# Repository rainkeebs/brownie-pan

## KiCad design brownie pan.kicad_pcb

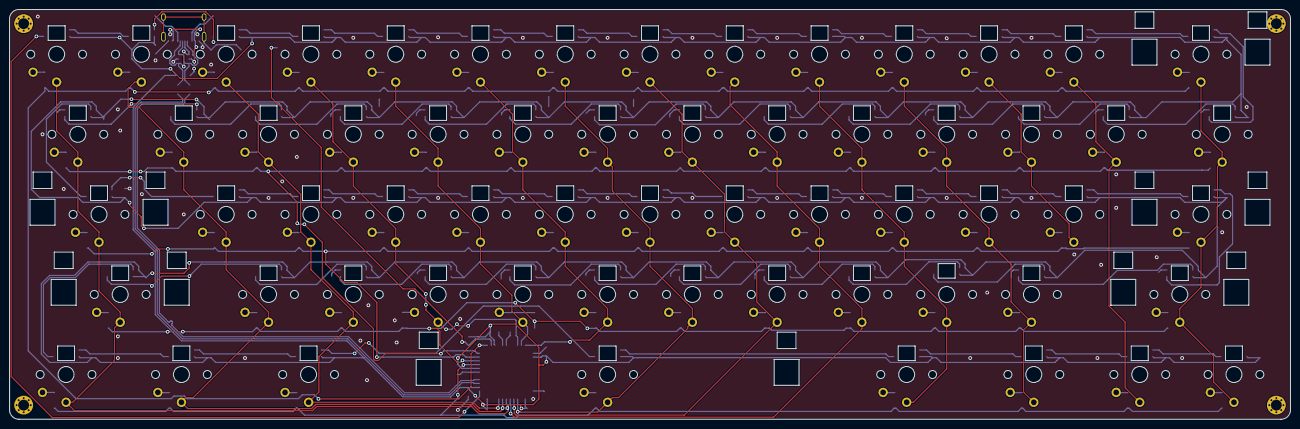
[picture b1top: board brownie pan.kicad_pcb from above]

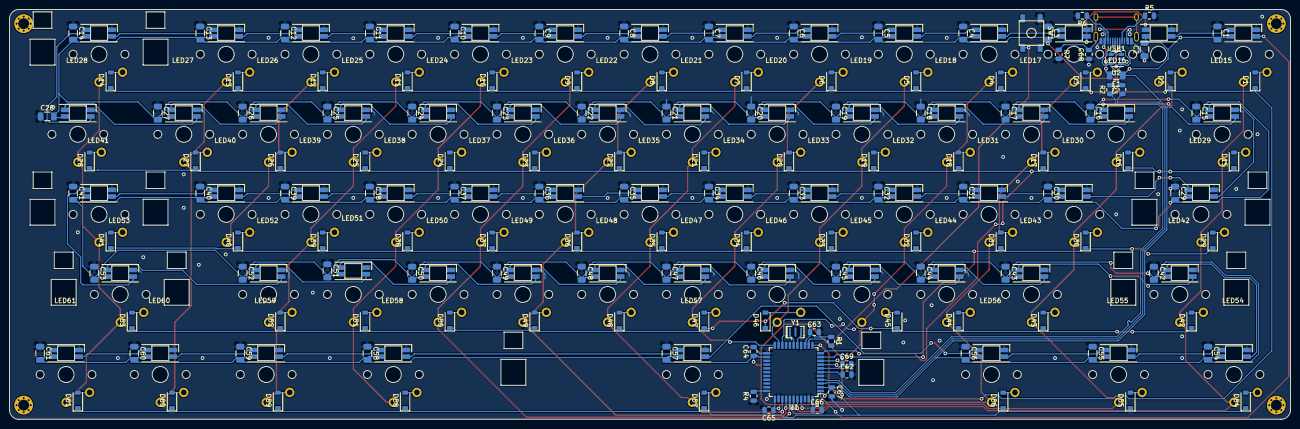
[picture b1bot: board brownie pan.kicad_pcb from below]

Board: 2 copper layers, 272.0 x 87.0 mm, 269 parts (204 on the bottom side), 156 nets.

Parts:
C1, C2, C3, C4, C5, C6, C7, C8, C9, C10, C11, C12, C13, C14, C15, C16, C17, C18, C19, C20, C21, C22, C23, C24, C25, C26, C27, C28, C29, C30, C31, C32, C33, C34, C35, C36, C37, C38, C39, C40, C41, C42, C43, C44, C45, C46, C47, C48, C49, C50, C51, C52, C53, C54, C55, C56, C57, C58, C59, C60, C61: 100uF; C_1206_3216Metric
C62: 1uF; C_0805_2012Metric
C63, C64, C65, C66, C69: 0.1uF; C_0805_2012Metric
C67: 10uF; C_0805_2012Metric
C68: 4.7n; C_0805_2012Metric
D1, D2, D3, D4, D5, D6, D7, D8, D9, D10, D11, D12, D13, D14, D15, D16, D17, D18, D19, D20, D21, D22, D23, D24, D25, D26, D27, D28, D29, D30, D31, D32, D33, D34, D35, D36, D37, D38, D39, D40, D41, D42, D43, D44, D45, D46, D47, D48, D49, D50, D51, D52, D53, D54, D55, D56, D57, D58, D59, D60, D61: D_Small; D_SOD-123
F1: 500mA; Fuse_1206_3216Metric
LED1, LED2, LED3, LED4, LED5, LED6, LED7, LED8, LED9, LED10, LED11, LED12, LED13, LED14, LED15, LED16, LED17, LED18, LED19, LED20, LED21, LED22, LED23, LED24, LED25, LED26, LED27, LED28, LED29, LED30, LED31, LED32, LED33, LED34, LED35, LED36, LED37, LED38, LED39, LED40, LED41, LED42, LED43, LED44, LED45, LED46, LED47, LED48, LED49, LED50, LED51, LED52, LED53, LED54, LED55, LED56, LED57, LED58, LED59, LED60, LED61: YS-SK6812MINI-E
MX1, MX2, MX3, MX4, MX5, MX6, MX7, MX8, MX9, MX10, MX11, MX12, MX13, MX16, MX17, MX18, MX19, MX20, MX21, MX22, MX23, MX24, MX25, MX26, MX27, MX30, MX31, MX32, MX33, MX34, MX35, MX36, MX37, MX38, MX39, MX40, MX43, MX44, MX45, MX46, MX47, MX48, MX49, MX50, MX51, MX52, MX60: MX-NoLED; 1u-choc
MX14, MX29, MX41: MX-NoLED; 2u-choc
MX15, MX28, MX55, MX56, MX58, MX59: MX-NoLED; 1.5u-choc
MX42, MX53: MX-NoLED; 2.5u-choc
MX54, MX61: MX-NoLED; 1.25u-choc
MX57: MX-NoLED; 5.5u-choc
R1, R4: 10k; R_0805_2012Metric
R2, R3: 22; R_0805_2012Metric
R5, R6: 5k1; R_0805_2012Metric
R7: 1M; R_0805_2012Metric
Ref**: Val**; M2_HOLE_v3
Ref**#2, Ref**#3, Ref**#4: Val**; M2_HOLE_v3
SW1: SW_Push; SKQG-1155865
U1: ATmega32U4-AU; TQFP-44_10x10mm_P0.8mm
U2: SRV05-4; SOT-23-6
USB1: HRO-TYPE-C-31-M-12
Y1: Resonator_Small; Resonator_SMD_muRata_CSTxExxV-3Pin_3.0x1.1mm

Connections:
+5V: C1.2, C2.2, C3.2, C4.2, C5.2, C6.2, C7.2, C8.2, C9.2, C10.2, C11.2, C12.2, C13.2, C14.2, C15.2, C16.2, C17.2, C18.2, C19.2, C20.2, C21.2, C22.2, C23.2, C24.2, C25.2, C26.2, C27.2, C28.2, C29.2, C30.2, C31.2, C32.2, C33.2, C34.2, C35.2, C36.2, C37.2, C38.2, C39.2, C40.2, C41.2, C42.2, C43.2, C44.2, C45.2, C46.2, C47.2, C48.2, C49.2, C50.2, C51.2, C52.2, C53.2, C54.2, C55.2, C56.2, C57.2, C58.2, C59.2, C60.2, C61.2, C63.1, C64.1, C65.1, C66.1, C67.1, C69.1, F1.1, LED1.1, LED2.1, LED3.1, LED4.1, LED5.1, LED6.1, LED7.1, LED8.1, LED9.1, LED10.1, LED11.1, LED12.1, LED13.1, LED14.1, LED15.1, LED16.1, LED17.1, LED18.1, LED19.1, LED20.1, LED21.1, LED22.1, LED23.1, LED24.1, LED25.1, LED26.1, LED27.1, LED28.1, LED29.1, LED30.1, LED31.1, LED32.1, LED33.1, LED34.1, LED35.1, LED36.1, LED37.1, LED38.1, LED39.1, LED40.1, LED41.1, LED42.1, LED43.1, LED44.1, LED45.1, LED46.1, LED47.1, LED48.1, LED49.1, LED50.1, LED51.1, LED52.1, LED53.1, LED54.1, LED55.1, LED56.1, LED57.1, LED58.1, LED59.1, LED60.1, LED61.1, R1.1, U1.2, U1.7, U1.14, U1.24, U1.34, U1.44
D+: R2.2, U2.3, U2.6, USB1.6, USB1.8
D-: R3.2, U2.1, U2.4, USB1.5, USB1.7
DP+: R2.1, U1.4
DP-: R3.1, U1.3
GND: C1.1, C2.1, C3.1, C4.1, C5.1, C6.1, C7.1, C8.1, C9.1, C10.1, C11.1, C12.1, C13.1, C14.1, C15.1, C16.1, C17.1, C18.1, C19.1, C20.1, C21.1, C22.1, C23.1, C24.1, C25.1, C26.1, C27.1, C28.1, C29.1, C30.1, C31.1, C32.1, C33.1, C34.1, C35.1, C36.1, C37.1, C38.1, C39.1, C40.1, C41.1, C42.1, C43.1, C44.1, C45.1, C46.1, C47.1, C48.1, C49.1, C50.1, C51.1, C52.1, C53.1, C54.1, C55.1, C56.1, C57.1, C58.1, C59.1, C60.1, C61.1, C62.2, C63.2, C64.2, C65.2, C66.2, C67.2, C68.1, C69.2, LED1.3, LED2.3, LED3.3, LED4.3, LED5.3, LED6.3, LED7.3, LED8.3, LED9.3, LED10.3, LED11.3, LED12.3, LED13.3, LED14.3, LED15.3, LED16.3, LED17.3, LED18.3, LED19.3, LED20.3, LED21.3, LED22.3, LED23.3, LED24.3, LED25.3, LED26.3, LED27.3, LED28.3, LED29.3, LED30.3, LED31.3, LED32.3, LED33.3, LED34.3, LED35.3, LED36.3, LED37.3, LED38.3, LED39.3, LED40.3, LED41.3, LED42.3, LED43.3, LED44.3, LED45.3, LED46.3, LED47.3, LED48.3, LED49.3, LED50.3, LED51.3, LED52.3, LED53.3, LED54.3, LED55.3, LED56.3, LED57.3, LED58.3, LED59.3, LED60.3, LED61.3, R4.1, R5.2, R6.2, R7.2, SW1.1, U1.5, U1.15, U1.23, U1.35, U1.43, U2.2, USB1.1, USB1.12, Y1.2
unnamed: C62.1, U1.6
unnamed: C68.2, R7.1, USB1.13
unnamed: D1.2, MX1.2
unnamed: D2.2, MX2.2
unnamed: D3.2, MX3.2
unnamed: D4.2, MX4.2
unnamed: D5.2, MX5.2
unnamed: D6.2, MX6.2
unnamed: D7.2, MX7.2
unnamed: D8.2, MX8.2
unnamed: D9.2, MX9.2
unnamed: D10.2, MX10.2
unnamed: D11.2, MX11.2
unnamed: D12.2, MX12.2
unnamed: D13.2, MX13.2
unnamed: D14.2, MX14.2
unnamed: D15.2, MX15.2
unnamed: D16.2, MX16.2
unnamed: D17.2, MX17.2
unnamed: D18.2, MX18.2
unnamed: D19.2, MX19.2
unnamed: D20.2, MX20.2
unnamed: D21.2, MX21.2
unnamed: D22.2, MX22.2
unnamed: D23.2, MX23.2
unnamed: D24.2, MX24.2
unnamed: D25.2, MX25.2
unnamed: D26.2, MX26.2
unnamed: D27.2, MX27.2
unnamed: D28.2, MX28.2
unnamed: D29.2, MX29.2
unnamed: D30.2, MX30.2
unnamed: D31.2, MX31.2
unnamed: D32.2, MX32.2
unnamed: D33.2, MX33.2
unnamed: D34.2, MX34.2
unnamed: D35.2, MX35.2
unnamed: D36.2, MX36.2
unnamed: D37.2, MX37.2
unnamed: D38.2, MX38.2
unnamed: D39.2, MX39.2
unnamed: D40.2, MX40.2
unnamed: D41.2, MX41.2
unnamed: D42.2, MX42.2
unnamed: D43.2, MX43.2
unnamed: D44.2, MX44.2
unnamed: D45.2, MX45.2
unnamed: D46.2, MX46.2
unnamed: D47.2, MX47.2
unnamed: D48.2, MX48.2
unnamed: D49.2, MX49.2
unnamed: D50.2, MX50.2
unnamed: D51.2, MX51.2
unnamed: D52.2, MX52.2
unnamed: D53.2, MX53.2
unnamed: D54.2, MX54.2
unnamed: D55.2, MX55.2
unnamed: D56.2, MX56.2
unnamed: D57.2, MX57.2
unnamed: D58.2, MX58.2
unnamed: D59.2, MX59.2
unnamed: D60.2, MX60.2
unnamed: D61.2, MX61.2
unnamed: LED1.2, LED2.4
unnamed: LED2.2, LED3.4
unnamed: LED3.2, LED4.4
unnamed: LED4.2, LED5.4
unnamed: LED5.2, LED6.4
unnamed: LED6.2, LED7.4
unnamed: LED7.2, LED8.4
unnamed: LED8.2, LED9.4
unnamed: LED10.2, LED11.4
unnamed: LED9.2, LED10.4
unnamed: LED11.2, LED12.4
unnamed: LED12.2, LED13.4
unnamed: LED13.2, LED14.4
unnamed: LED14.2, LED28.4
unnamed: LED15.2, LED29.4
unnamed: LED15.4, LED16.2
unnamed: LED16.4, LED17.2
unnamed: LED17.4, LED18.2
unnamed: LED18.4, LED19.2
unnamed: LED19.4, LED20.2
unnamed: LED20.4, LED21.2
unnamed: LED21.4, LED22.2
unnamed: LED22.4, LED23.2
unnamed: LED23.4, LED24.2
unnamed: LED24.4, LED25.2
unnamed: LED25.4, LED26.2
unnamed: LED26.4, LED27.2
unnamed: LED27.4, LED28.2
unnamed: LED29.2, LED30.4
unnamed: LED30.2, LED31.4
unnamed: LED31.2, LED32.4
unnamed: LED32.2, LED33.4
unnamed: LED33.2, LED34.4
unnamed: LED34.2, LED35.4
unnamed: LED35.2, LED36.4
unnamed: LED36.2, LED37.4
unnamed: LED37.2, LED38.4
unnamed: LED38.2, LED39.4
unnamed: LED39.2, LED40.4
unnamed: LED40.2, LED41.4
unnamed: LED41.2, LED53.4
unnamed: LED42.2, LED54.4
unnamed: LED42.4, LED43.2
unnamed: LED43.4, LED44.2
unnamed: LED44.4, LED45.2
unnamed: LED45.4, LED46.2
unnamed: LED46.4, LED47.2
unnamed: LED47.4, LED48.2
unnamed: LED48.4, LED49.2
unnamed: LED49.4, LED50.2
unnamed: LED50.4, LED51.2
unnamed: LED51.4, LED52.2
unnamed: LED52.4, LED53.2
unnamed: LED54.2, LED55.4
unnamed: LED55.2, LED56.4
unnamed: LED56.2, LED57.4
unnamed: LED57.2, LED58.4
unnamed: LED58.2, LED59.4
unnamed: LED59.2, LED60.4
unnamed: LED60.2, LED61.4
unnamed: R1.2, SW1.2, U1.13
unnamed: R4.2, U1.33
unnamed: R5.1, USB1.4
unnamed: R6.1, USB1.10
unnamed: U1.16, Y1.3
unnamed: U1.17, Y1.1
RGB: LED1.4, U1.1
VCC: F1.2, U2.5, USB1.2, USB1.11
col0: MX1.1, MX15.1, MX29.1, MX42.1, MX54.1, U1.39
col1: MX2.1, MX16.1, MX30.1, MX43.1, MX55.1, U1.40
col2: MX3.1, MX17.1, MX31.1, MX44.1, MX56.1, U1.41
col3: MX4.1, MX18.1, MX32.1, MX45.1, U1.20
col4: MX5.1, MX19.1, MX33.1, MX46.1, U1.21
col5: MX6.1, MX20.1, MX34.1, MX47.1, U1.22
col6: MX7.1, MX21.1, MX35.1, MX48.1, MX57.1, U1.36
col7: MX8.1, MX22.1, MX36.1, MX49.1, U1.37
col8: MX9.1, MX23.1, MX37.1, MX50.1, U1.38
col9: MX10.1, MX24.1, MX38.1, MX51.1, MX58.1
col10: MX11.1, MX25.1, MX39.1, MX52.1, MX59.1
col11: MX12.1, MX26.1, MX40.1
col12: MX13.1, MX27.1, MX60.1
col13: MX14.1, MX28.1, MX41.1, MX53.1, MX61.1
row0: D1.1, D2.1, D3.1, D4.1, D5.1, D6.1, D7.1, D8.1, D9.1, D10.1, D11.1, D12.1, D13.1, D14.1, U1.12
row1: D15.1, D16.1, D17.1, D18.1, D19.1, D20.1, D21.1, D22.1, D23.1, D24.1, D25.1, D26.1, D27.1, D28.1, U1.11
row2: D29.1, D30.1, D31.1, D32.1, D33.1, D34.1, D35.1, D36.1, D37.1, D38.1, D39.1, D40.1, D41.1, U1.10
row3: D42.1, D43.1, D44.1, D45.1, D46.1, D47.1, D48.1, D49.1, D50.1, D51.1, D52.1, D53.1, U1.9
row4: D54.1, D55.1, D56.1, D57.1, D58.1, D59.1, D60.1, D61.1, U1.8
